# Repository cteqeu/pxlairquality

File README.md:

# Hogeschool PXL NB-IoT Air Quality Project 

[![PXL University College Logo][PXL-logo]][PXL-link]

## Inhoudstafel

## Introductie

Repository voor het PXL NB-IoT Air Quality Project.

## Source Roadmap 

```
General   Bevat de slides, data sheets, ... .

Hardware  Bevat informatie over de hardware.

Misc      Bavat extra bestanden zoals foto's.

Software  Bevast informatie over de software en voorbeeld programms, ... .
```

## Contributors

- [Vincent Claes][Vincent-linkedin]
- [Bryan Honof][Bryan-linkedin]

[PXL-logo]: ./Misc/images/pxl-logo.png "PXL logo"
[PXL-link]: https://www.pxl.be
[Vincent-linkedin]: https://www.linkedin.com/in/vincentclaes/
[Vincent-mail]: Vicent.Claes@pxl.be
[Bryan-linkedin]: https://www.linkedin.com/in/bryan-honof/
[Bryan-mail]: Bryan.Honof@student.pxl.be

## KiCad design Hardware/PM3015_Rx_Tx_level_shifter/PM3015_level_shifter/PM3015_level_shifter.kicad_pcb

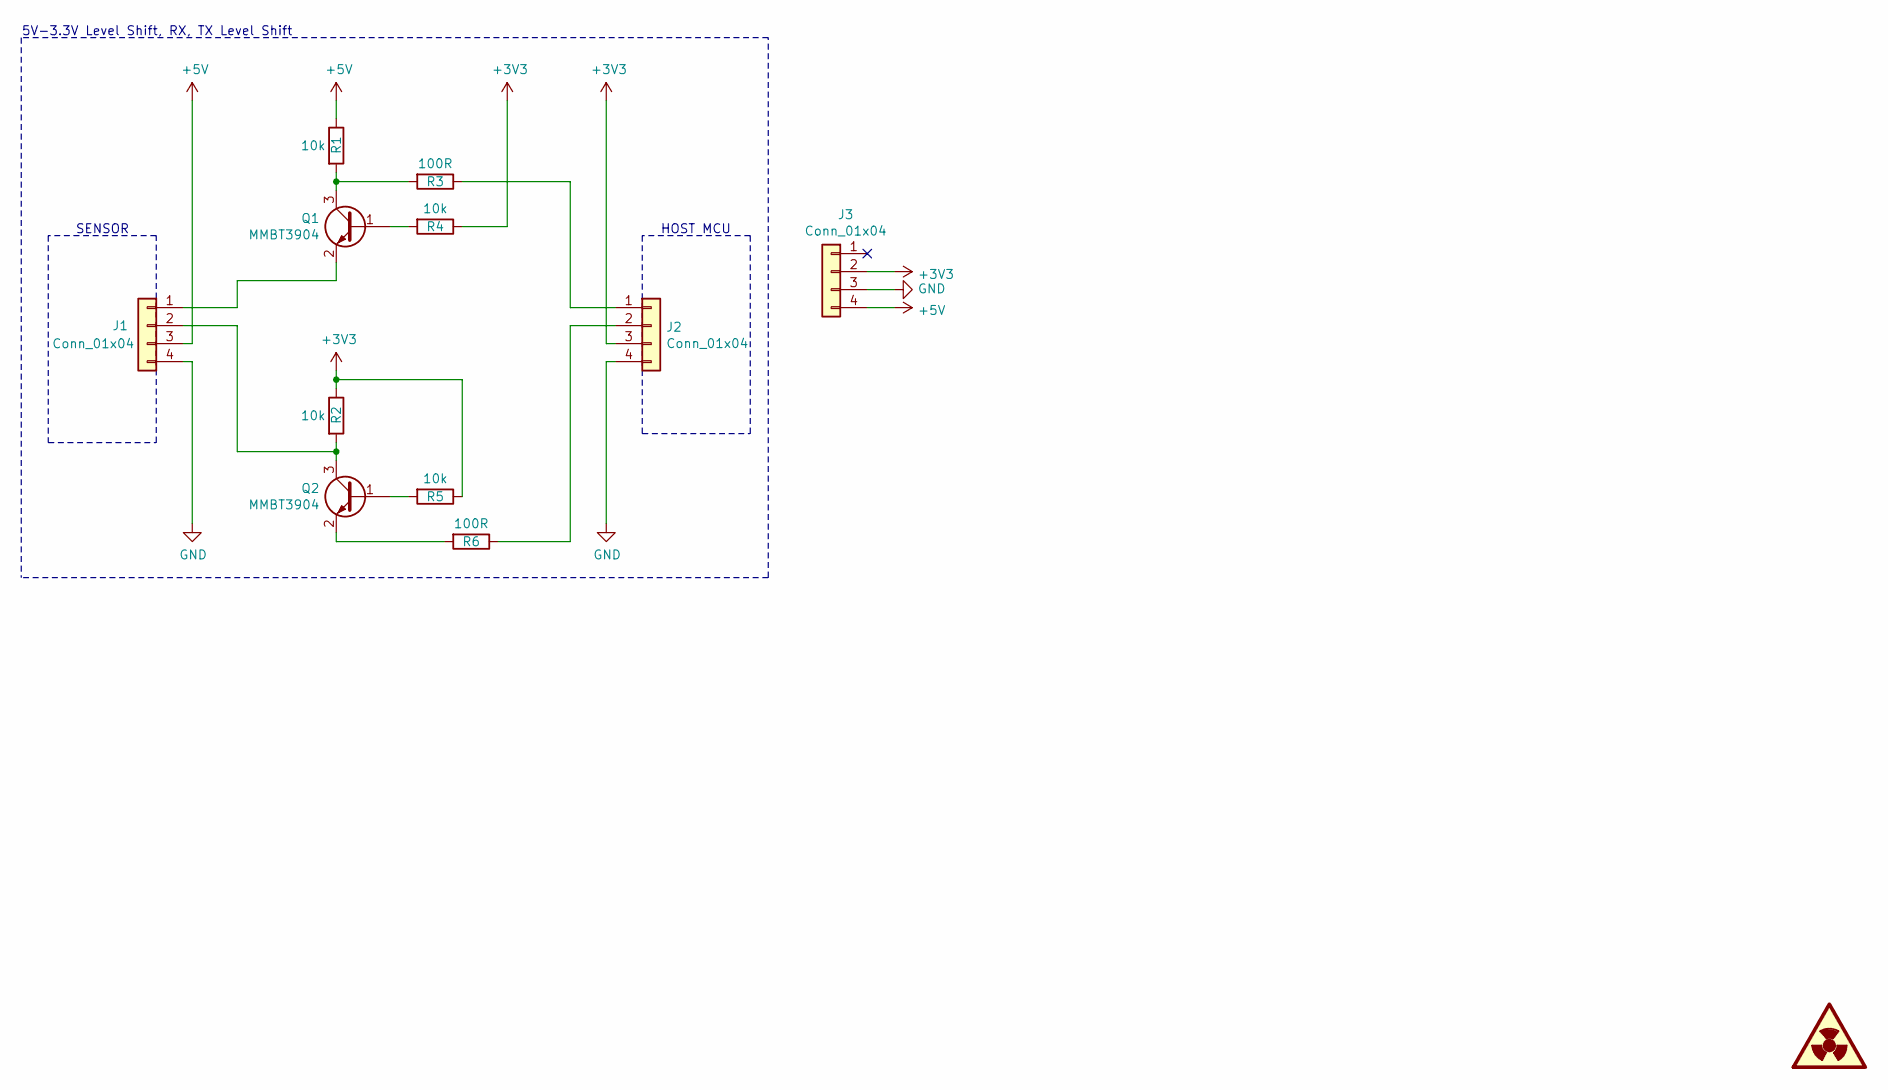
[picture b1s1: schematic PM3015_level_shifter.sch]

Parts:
J1, J2, J3: Conn_01x04; PinHeader_1x04_P2.54mm_Vertical
Q1, Q2: MMBT3904; SOT-23
R1, R2, R4, R5: 10k; R_0805_2012Metric_Pad1.15x1.40mm_HandSolder
R3, R6: 100R; R_0805_2012Metric_Pad1.15x1.40mm_HandSolder

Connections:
+3V3: J2.3, J3.2, R2.1, R4.1, R5.1
+5V: J1.3, J3.4, R1.1
GND: J1.4, J2.4, J3.3
unnamed: J1.1, Q1.2 (E)
unnamed: J1.2, Q2.3 (C), R2.2
unnamed: J2.1, R3.1
unnamed: J2.2, R6.1
unnamed: Q1.1 (B), R4.2
unnamed: Q1.3 (C), R1.2, R3.2
unnamed: Q2.1 (B), R5.2
unnamed: Q2.2 (E), R6.2

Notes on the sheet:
HOST MCU
SENSOR
5V-3.3V Level Shift, RX, TX Level Shift

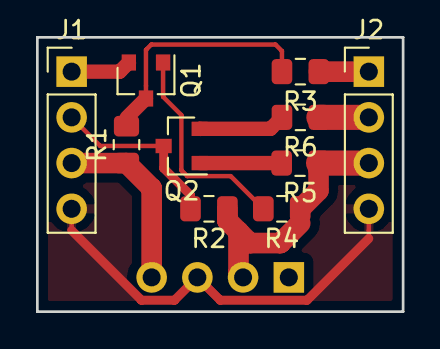
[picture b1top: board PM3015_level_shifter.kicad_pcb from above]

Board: 2 copper layers, 20.3 x 15.2 mm, 11 parts (1 on the bottom side), 11 nets.

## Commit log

2019-02-06 6022019
    Slides 28012019 added and datasheet for Air Quality Sensor
2019-02-08 First Examples available
    Datasheets, First Examples, Arduino packages,...
2019-02-15 Added a testing map for prototyping
2019-02-16 Cleaned up directory
2019-02-16 Renamed "Arduino Libraries" -> "Arduino_Libraries"
2019-02-16 Renamed "SODAQ MBili Examples" -> "SODAQ_MBili_Examples"
2019-02-16 Started first tests Added ATmega1284P Data sheet (Chip on the SODAQ Mbili board)
2019-02-16 new file: Software/Arduino_Libraries/app/app_defs.h
2019-02-16 Added sub module for for the arduino-nbiot-rdk repo
2019-02-16 Added sub module for arduino-nbiot-sdk
2019-02-16 Added PXL logo to readme
2019-02-16 modified: README.md
2019-02-16 new file: Misc/images/pxl-logo.png modified: README.md
2019-02-16 Added pxl.be link on image
2019-02-16 Finished GPS functionality. GPS values can be read and send to the server.
2019-02-16 Added TPH v2 functionallity
2019-02-17 Added possibility to GET asset states from devices trough curl.
2019-02-17 Preparing POST option in script.
2019-02-17 Added functionality to get latest asset state and aggregated data.
2019-02-17 renamed: test.sh -> allthingsapi.sh
2019-02-17 Started working on making the app's logic into its own class.
2019-02-17 Cleaning up readme
2019-02-17 Started work on PM3015 drive circuit.
2019-02-18 Set theme jekyll-theme-architect
2019-02-18 Slides upload
    Slides upload
2019-02-19 Did something cannot remember what :).
2019-02-19 Started working on PM3015 class.
2019-02-19 Added to PM3015 class
2019-02-19 Got the PM3015 to work.
2019-02-19 Worked on PM3015 class.
2019-02-26 modified: Software/app/app.ino
2019-02-26 Fixed README.md.
2019-02-26 deleted: _config.yml
2019-02-28 Worked on the class.
2019-03-09 Restructured App.
2019-03-09 Added git ignore rule.
2019-03-10 Added git & github presentation.
2019-03-10 Worked the App class. Fixed some warnings.
2019-03-12 modified: Software/app/app.ino modified: Software/app/libraries/App/App.h modified: Software/app/libraries/App/PM3015.cpp modified: Software/app/libraries/App/PM3015.h
2019-03-12 Added templates for example projects.
2019-03-12 Finished PM3015 Laser Particle Sensor Module example.
2019-03-12 Added comments.
2019-03-12 Finished Custom Payload example.
2019-03-12 modified: Arduino_Libraries/arduino-nbiot-sdk
2019-03-14 Added photo's and videos for wiki.
2019-03-14 Added more pictures.
2019-03-14 README vertaalt naar NL.
2019-04-02 Cleaned up the images
2019-04-02 Started on node-red
2019-04-02 deleted: Misc/images/PM3015_connector.png
2019-04-02 modified: README.md new file: app.json
2019-04-02 renamed: Software/Node-RED/app.json -> app.json
2019-04-25 Dashboard tutorial deel 1
2019-04-29 dasboard deel 2 configuratie
2019-04-29 Updated app.
2019-04-29 replaced Node-RED software directory for repo submodule.
2019-11-06 Update issue templates
2019-12-05 Added an overview where you can see the contents of each kit
    The file has conditional formatting. When you place x = green , o = red , which means component is in the kit or not.
2019-12-06 Delete .DS_Store and add to .gitignore
    Keep your repo clean. `.DS_Store` is only useful on mac for that
    specific person that created it (finder automatically creates it).
2020-01-03 Add Demo Code
2020-01-04 Add TPH Sensor
2020-01-17 Upload 17012020
2020-01-17 Restructuring
2020-01-20 Add nb-IOT integration
